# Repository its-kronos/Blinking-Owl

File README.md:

# Blinking-Owl
An astable multivibrator with flashing LEDs that serve as eyes for an owl.

# Schematic

# PCB

## Front

## Back

# BOM

- (2) CR2032 Battery Cell Holders
- (8) 4.7k Ohm Resistors
- (4) 47k Ohm Resistors
- (2) 10 uF Capacitors
- (2) LEDs
- (2) PNP Transistors

# Afterword
- After receiving the parts for the Hackclub "Solder" program, I was surprised that there were (12) 220 ohm resistors and (6) of the 4.7K and 47K ohm resisters, which wasn't explicitly made clear. This taught me that it's always a good idea to double check the available materials to avoid requiring substitutions.
- After ordering the PCB, the parts came around five days later. When I build a prototype on a breadboard, the LEDs wouldn't light up with 5 volts in series, but would only work in parallel, contrary to what a simulation on Falstad showed me. This taught me that it is often better to wire voltage-dependant things in parallel to avoid issues like these. It also helped to understand that even if it takes longer for a build to be completed, prototyping something in real life on something like a breadboard is important to make sure that there are no problems down the road.
- I still figured out a way to make the current PCB work out with the current wiring, which was by adding two wires to connect corresponding legs of the two LEDs while scratching out the currect trace that connected them. Keeping this trace would allow current to flow backwards in an unintended direction to directly go through wires or traces, keeping the LEDs unlit.

# Demonstrations

## Prototype
https://vimeo.com/1090699929/9bd934338b?share=copy

## Assembly
https://vimeo.com/1093416475/6044e68823?share=copy

# Attributions
\- Created by its_kronos

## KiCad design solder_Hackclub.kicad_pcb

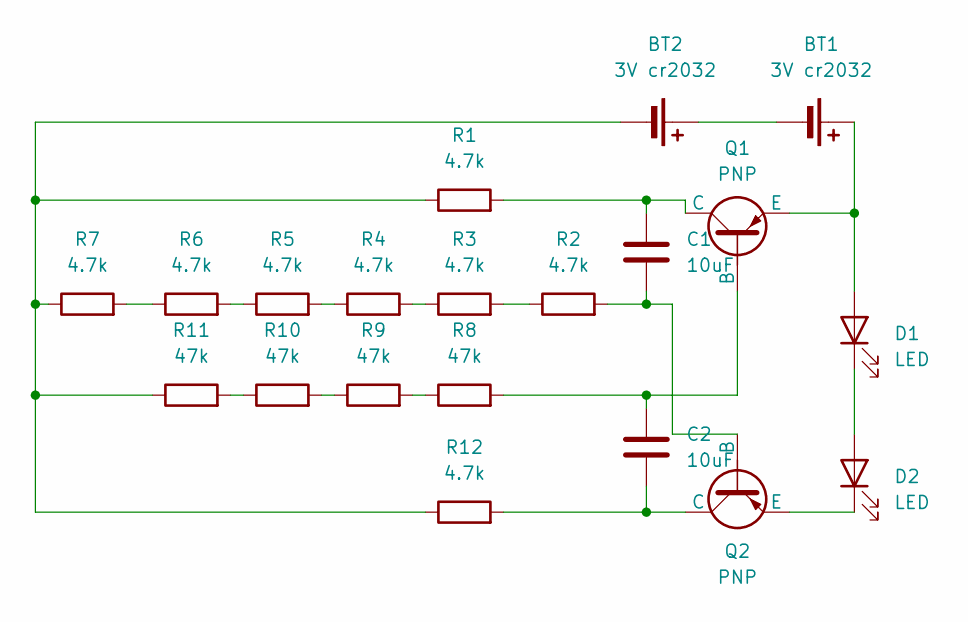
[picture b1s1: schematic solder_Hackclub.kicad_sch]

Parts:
BT1, BT2: 3V cr2032; BatteryHolder_Keystone_3034_1x20mm
C1, C2: 10uF; CP_Radial_D8.0mm_P5.00mm
D1, D2: LED; LED_D5.0mm
Q1, Q2: PNP; TO-92L_HandSolder
R1, R2, R3, R4, R5, R6, R7, R12: 4.7k; R_Axial_DIN0207_L6.3mm_D2.5mm_P7.62mm_Horizontal
R8, R9, R10, R11: 47k; R_Axial_DIN0207_L6.3mm_D2.5mm_P7.62mm_Horizontal

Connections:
unnamed: BT1.1 (+), D1.2 (A), Q1.3 (E)
unnamed: BT1.2 (-), BT2.1 (+)
unnamed: BT2.2 (-), R1.1, R7.1, R11.1, R12.1
unnamed: D1.1 (K), D2.2 (A)
unnamed: D2.1 (K), Q2.3 (E)
unnamed: C2.1, Q1.2 (B), R8.2
unnamed: C1.1, Q1.1 (C), R1.2
unnamed: C1.2, Q2.2 (B), R2.2
unnamed: C2.2, Q2.1 (C), R12.2
unnamed: R2.1, R3.2
unnamed: R3.1, R4.2
unnamed: R4.1, R5.2
unnamed: R5.1, R6.2
unnamed: R6.1, R7.2
unnamed: R8.1, R9.2
unnamed: R10.1, R11.2
unnamed: R9.1, R10.2

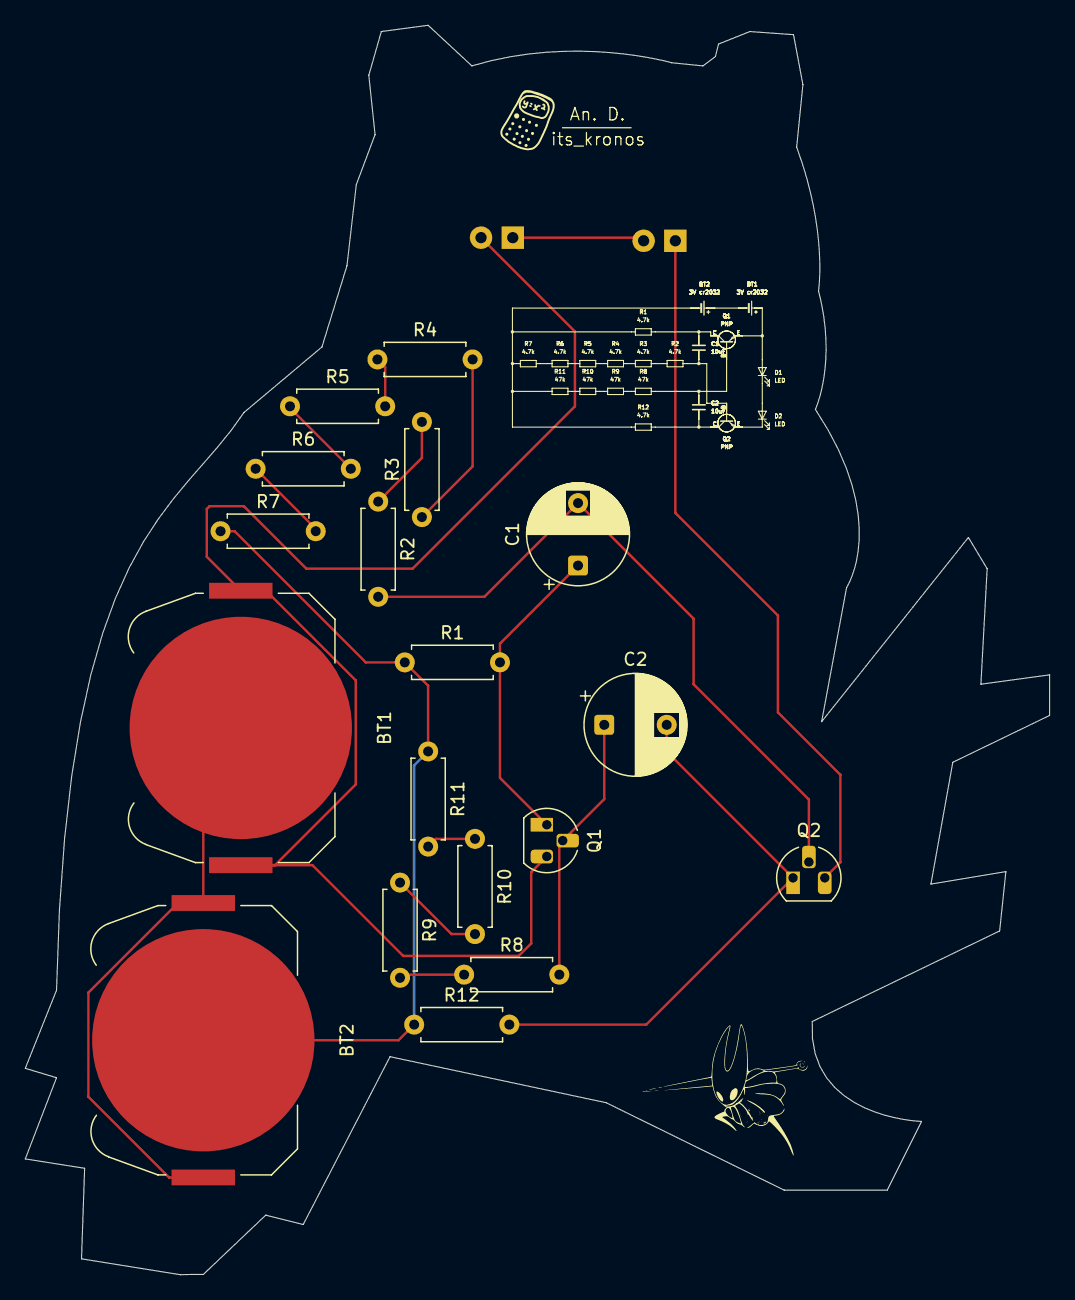
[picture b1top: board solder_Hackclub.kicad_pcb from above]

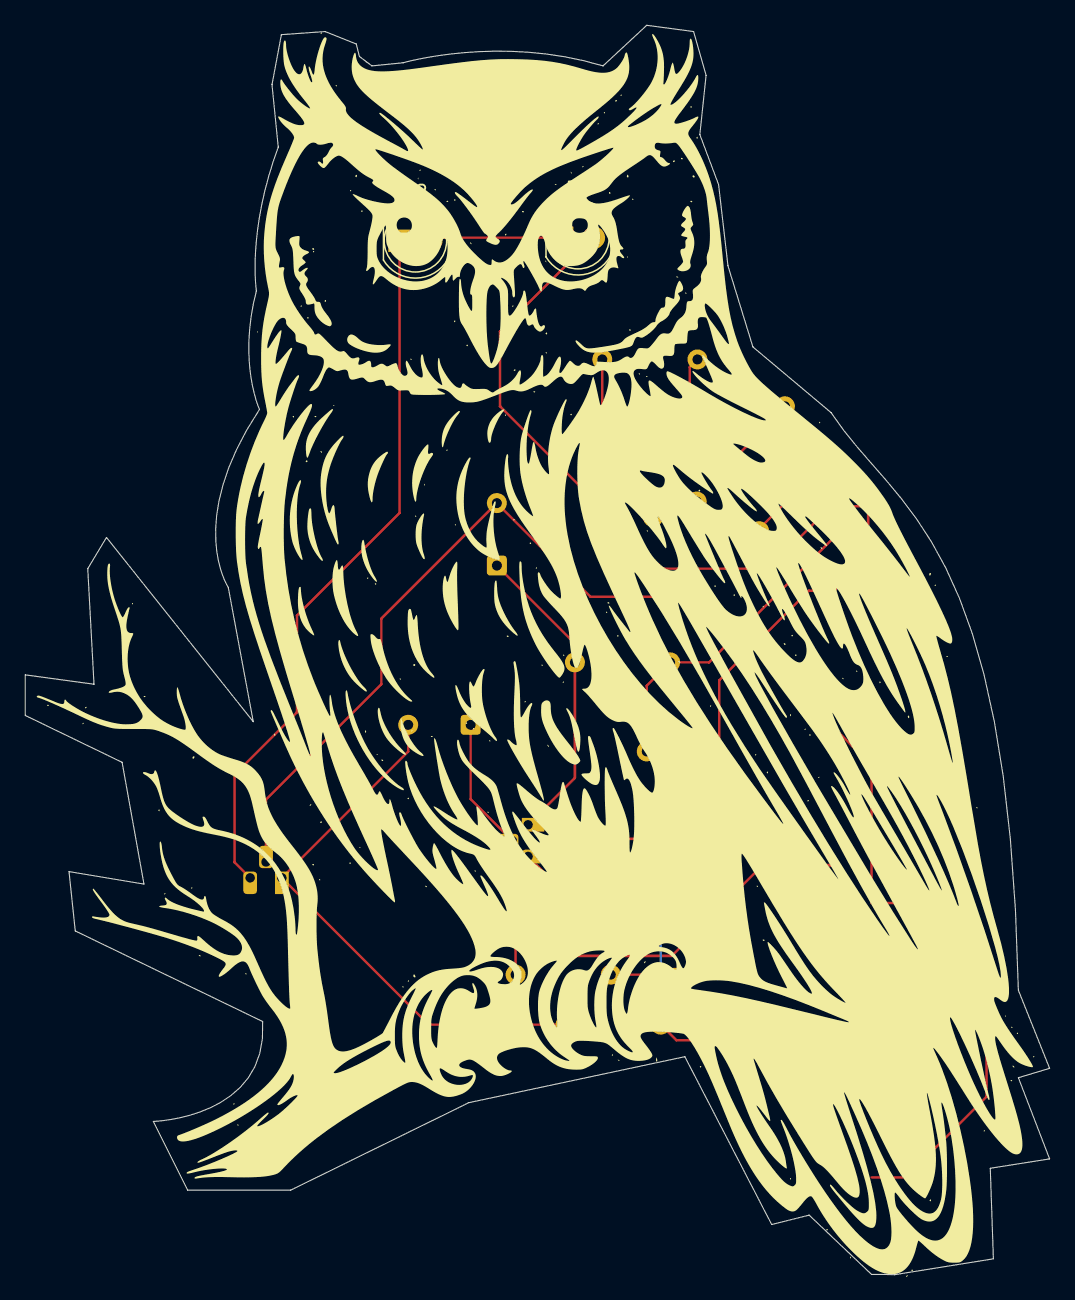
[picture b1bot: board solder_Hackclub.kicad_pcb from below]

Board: 2 copper layers, 82.0 x 100.0 mm, 20 parts (2 on the bottom side), 17 nets.

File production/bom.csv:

Designator,Footprint,Quantity,Value,LCSC Part #
"BT1, BT2",BatteryHolder_Keystone_3034_1x20mm,2,3V cr2032,
"C1, C2",CP_Radial_D8.0mm_P5.00mm,2,10uF,
"D1, D2",LED_D5.0mm,2,LED,
"Q1, Q2",TO-92L_HandSolder,2,PNP,
"R1, R12, R2, R3, R4, R5, R6, R7",R_Axial_DIN0207_L6.3mm_D2.5mm_P7.62mm_Horizontal,8,4.7k,
"R10, R11, R8, R9",R_Axial_DIN0207_L6.3mm_D2.5mm_P7.62mm_Horizontal,4,47k,

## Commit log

2025-05-22 Create src
2025-05-22 Create e
2025-05-28 Add folders
2025-06-15 Update README.md - add assembly video
